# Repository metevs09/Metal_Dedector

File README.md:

# Metal Detector Project

This project provides a comprehensive reference for building a pulse induction metal detector. It includes the general system scheme, hardware design files, PCB designs, CAM files for manufacturing, and a USB to UART module for ESP32 integration.

## Overview
The Metal Detector project is designed to help enthusiasts and professionals understand and implement a pulse induction metal detector. The repository contains:

- General Scheme: Detailed system and hardware schematics.
- PCB Design Files: Ready-to-use designs for fabricating the circuit board.
- CAM Files: Files required for computer-aided manufacturing.
- ESP32 Integration: A USB to UART module for connecting the detector to an ESP32 microcontroller.
## Features
- Pulse Induction Operation: Implements the principles of pulse induction metal detection.
- Detailed Schematics: Complete general and hardware design documents.
- PCB and CAM Files: Design files for PCB manufacturing and assembly.
- ESP32 Interface: Provides a USB to UART bridge for interfacing with ESP32-based systems.
  
## Repository Structure
```
Metal_Dedector/
- ├── CAM file/              # CAM files for PCB manufacturing
- ├── PCB files/             # PCB design files and layouts
- ├── USB to UART for ESP32/  # Interface files for ESP32 integration
- ├── Metal Dedektör.drawio   # Schematic diagram created with draw.io
- ├── README.md              # This README file
- └── SECURITY.md            # Security policy information
```
## Getting Started

### Prerequisites

#### Electronics Knowledge:
- Basic understanding of electronics and PCB design.
#### Software Tools:
- Draw.io for viewing and editing schematics.
- PCB design software (such as Eagle or KiCad) for viewing the PCB files.
- A computer with a USB interface for using the ESP32 integration module.
### Installation
#### Clone the Repository:
```git clone https://github.com/metevs09/Metal_Dedector.git```

#### Review the Design Files:
- Open Metal Dedektör.drawio with Draw.io to view the schematic.
- Check the PCB files in the PCB files/ directory.
- Refer to the files in USB to UART for ESP32/ for ESP32 interfacing details.
#### Manufacture and Assemble:
- Use the CAM files to prepare your PCB for manufacturing.
- Assemble the components following standard electronic assembly practices.
### Usage
Once the hardware is assembled:

1. Connect the ESP32 via the USB to UART interface.
2. Use your preferred development environment to load and run firmware.
3. Test the metal detector according to the provided schematic and design guidelines.
> Note: Always follow proper safety procedures when working with electronic circuits and during the assembly process.

License
This project is licensed under the MIT License. See the LICENSE file for more details.

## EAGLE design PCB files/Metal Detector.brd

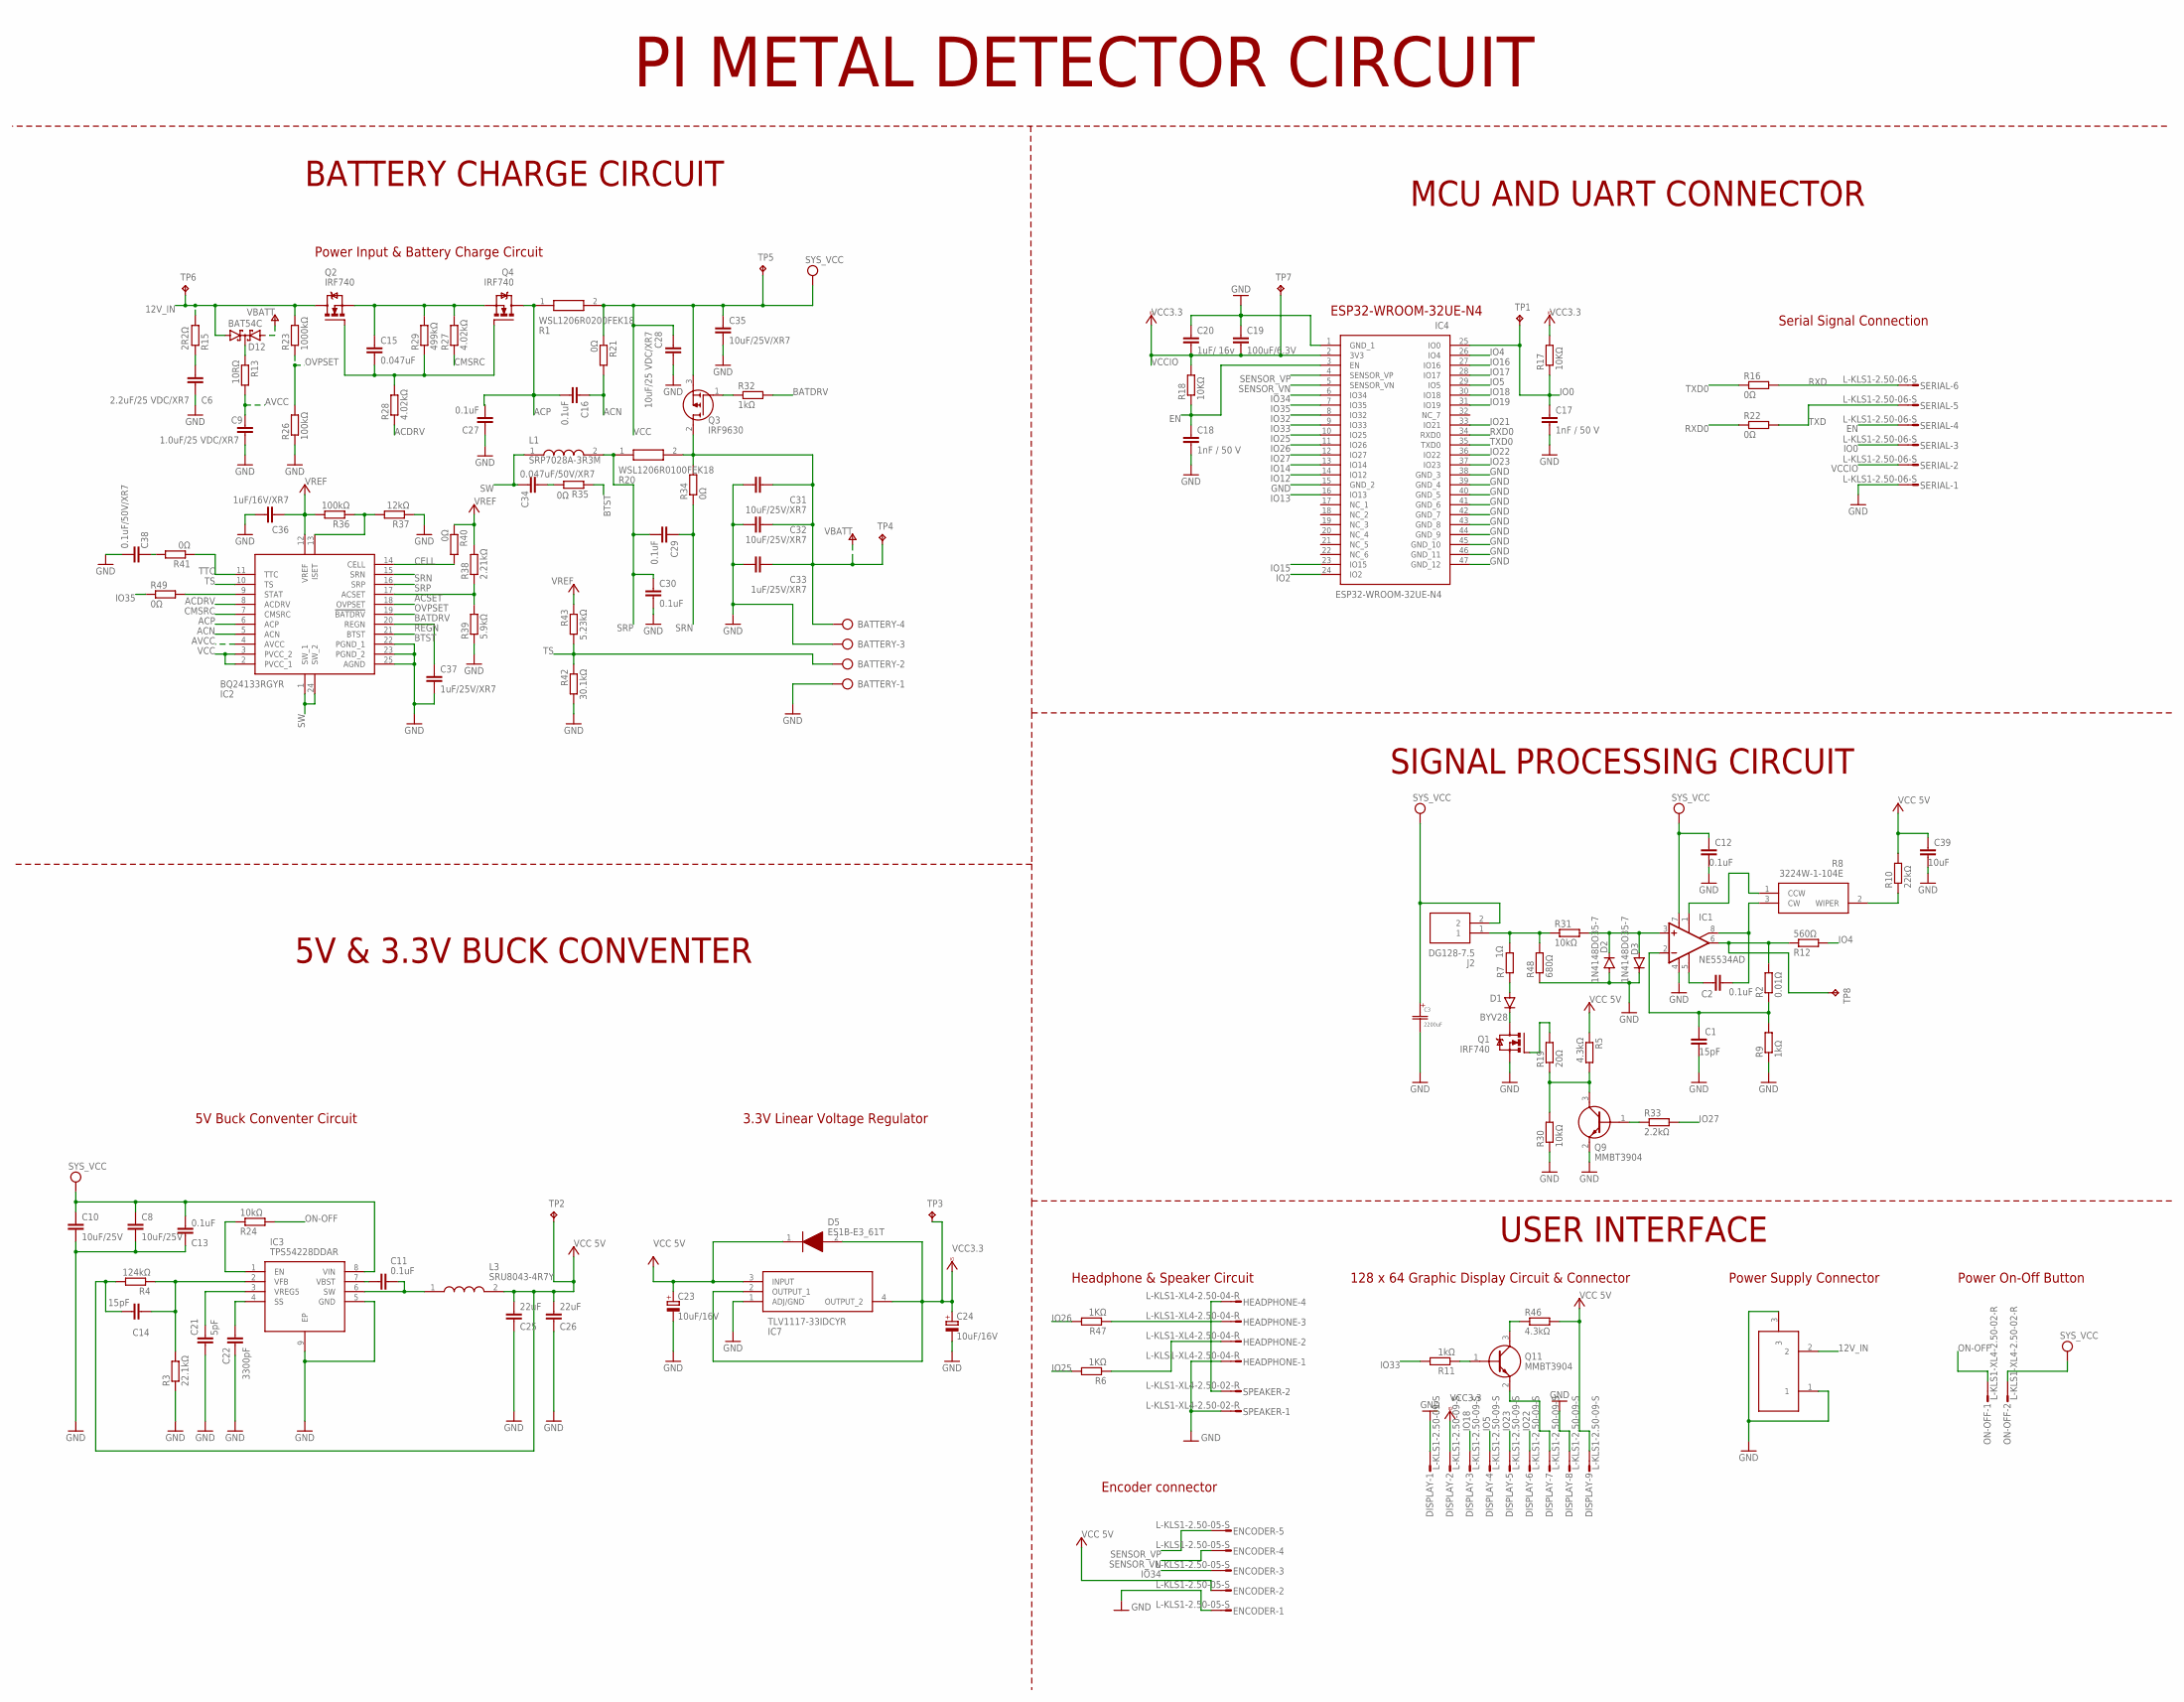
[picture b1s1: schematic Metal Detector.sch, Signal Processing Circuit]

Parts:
12VIN: DC21MMX; DC-21MM
BATTERY: AK500/4
C1, C14: 15pF; C0603
C2, C11, C12, C13, C16, C27, C29, C30: 0.1uF; C0603
C3: 2200uF; CAP_12.5_X_20_PAN
C6: 2.2uF/25 VDC/XR7; 1206
C8, C10: 10uF/25V; C1210
C9: 1.0uF/25 VDC/XR7; 1206
C15: 0.047uF; C0603
C17, C18: 1nF / 50 V; C0603
C19: 100uF/6.3V; C1206
C20: 1uF/ 16v; C0603
C21: 5pF; C0603
C22: 3300pF; C0603
C23, C24: 10uF/16V; PANASONIC_B
C25, C26: 22uF; 1206
C28: 10uF/25 VDC/XR7; 1206
C31, C32, C35: 10uF/25V/XR7; 1206
C33, C37: 1uF/25V/XR7; C0805
C34: 0.047uF/50V/XR7; C0603
C36: 1uF/16V/XR7; C0805
C38: 0.1uF/50V/XR7; C0603
C39: 10uF; C0603
D1: BYV28; SOD64-10
D2, D3: 1N4148DO35-7; DO35-7
D5: ES1B-E3_61T; DIOM5127X229N
D12: BAT54C; SOT23
DISPLAY: L-KLS1-2.50-09-S; S09P
ENCODER: L-KLS1-2.50-05-S; S05P
HEADPHONE: L-KLS1-XL4-2.50-04-R; S04P
IC1: NE5534AD; SO08
IC2: BQ24133RGYR
IC3: TPS54228DDAR; SOIC127P600X170-9N
IC4: ESP32-WROOM-32UE-N4; ESP32WROOM32UEN4
IC7: TLV1117-33IDCYR; SOT230P700X180-4N
J2: DG128-7.5; DG1287502P1400AH
L1: SRP7028A-3R3M; SRP7028A3R3M
L3: SRU8043-4R7Y; SRU8043330Y
ON-OFF: L-KLS1-XL4-2.50-02-R; S02P
Q1, Q2, Q4: IRF740; TO220BV
Q3: IRF9630; TO254P465X1024X2050-3P
Q9, Q11: MMBT3904; SOT95P240X120-3N
R1: WSL1206R0200FEK18; RESC3216X89N
R2: 0.01Ω; R1206
R3: 22.1kΩ; R0603
R4: 124kΩ; R0603
R5, R46: 4.3kΩ; R1206
R6, R47: 1KΩ; R0603
R7: 1Ω; 0207/10
R8: 3224W-1-104E; 3224W-1-105E
R9: 1kΩ; R1206
R10: 22kΩ; R1206
R11, R32: 1kΩ; R0603
R12: 560Ω; R0603
R13: 10RΩ; R1206
R15: 2R2Ω; R2010
R16, R21, R22, R34, R35, R40, R41, R49: 0Ω; R0603
R17, R18: 10KΩ; R0603
R19: 20Ω; R1206
R20: WSL1206R0100FEK18; RESC3216X89N
R23: 1000kΩ; R0603
R24: 10kΩ; R0603
R26, R36: 100kΩ; R0603
R27, R28: 4.02kΩ; R0603
R29: 499kΩ; R0603
R30, R31: 10kΩ; R1206
R33: 2.2kΩ; R1206
R37: 12kΩ; R0603
R38: 2.21kΩ; R0603
R39: 5.9kΩ; R0603
R42: 30.1kΩ; R0603
R43: 5.23kΩ; R0603
R48: 680Ω; R1206
SERIAL: L-KLS1-2.50-06-S; S06P
SPEAKER: L-KLS1-XL4-2.50-02-R; S02P
TP1, TP2, TP3, TP4, TP5, TP6, TP7, TP8: TPTP10R; TP10R

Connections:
12V_IN: 12VIN.2, D12.1 (A1), Q2.D, R15.2, R23.2, TP6.TP
ACDRV: IC2.8 (ACDRV), R28.1
ACN: C16.1, IC2.5 (ACN), R21.2
ACP: C16.2, C27.2, IC2.6 (ACP), Q4.D, R1.1
ACSET: IC2.17 (ACSET), R38.1, R39.2
AVCC: C9.1, IC2.4 (AVCC), R13.2
BATDRV: IC2.19 (!BATDRV), R32.2
BTST: IC2.21 (BTST), R35.1
CELL: IC2.14 (CELL), R40.2
CMSRC: IC2.7 (CMSRC), R27.1
EN: C18.1, IC4.3 (EN), R18.1, SERIAL.4
GND: 12VIN.1, 12VIN.3, BATTERY.1, BATTERY.3, C1.2, C3.2, C6.2, C8.2, C9.2, C10.2, C12.2, C13.2, C17.2, C18.2, C19.1, C20.1, C21.2, C22.2, C23.-, C24.-, C25.2, C26.2, C27.1, C28.2, C30.2, C31.2, C32.2, C33.2, C35.2, C36.1, C37.2, C38.2, C39.2, D2.A, D3.C, DISPLAY.1, DISPLAY.8, ENCODER.1, HEADPHONE.1, IC1.4 (V-), IC2.22 (PGND_1), IC2.23 (PGND_2), IC2.25 (AGND), IC3.5 (GND), IC3.9 (EP), IC4.1 (GND_1), IC4.15 (GND_2), IC4.38 (GND_3), IC4.39 (GND_4), IC4.40 (GND_5), IC4.41 (GND_6), IC4.42 (GND_7), IC4.43 (GND_8), IC4.44 (GND_9), IC4.45 (GND_10), IC4.46 (GND_11), IC4.47 (GND_12), IC7.1 (ADJ/GND), Q1.S, Q9.2 (E), R3.1, R9.1, R26.1, R30.1, R37.1, R39.1, R42.2, R48.1, SERIAL.1, SPEAKER.1
IO0: C17.1, IC4.25 (IO0), R17.1, SERIAL.3, TP1.TP
IO2: IC4.24 (IO2)
IO4: IC1.6 (OUT), IC4.26 (IO4), R2.2, R12.1, R12.2, TP8.TP
IO5: DISPLAY.4, IC4.29 (IO5)
IO12: IC4.14 (IO12)
IO13: IC4.16 (IO13)
IO14: IC4.13 (IO14)
IO15: IC4.23 (IO15)
IO16: IC4.27 (IO16)
IO17: IC4.28 (IO17)
IO18: DISPLAY.3, IC4.30 (IO18)
IO19: IC4.31 (IO19)
IO21: IC4.33 (IO21)
IO22: DISPLAY.6, IC4.36 (IO22)
IO23: DISPLAY.5, IC4.37 (IO23)
IO25: IC4.10 (IO25), R6.2
IO26: IC4.11 (IO26), R47.2
IO27: IC4.12 (IO27), R33.2
IO32: IC4.8 (IO32)
IO33: IC4.9 (IO33), R11.2
IO34: ENCODER.3, IC4.6 (IO34)
IO35: IC2.9 (STAT), IC4.7 (IO35), R49.1, R49.2
ISET: IC2.13 (ISET), R36.1, R37.2
unnamed: D2.C, D3.A, IC1.3 (+IN), R31.2
unnamed: Q1.G, R19.2
unnamed: Q9.3 (C), R5.2, R19.1, R30.2
unnamed: D1.A, R7.1
unnamed: Q9.1 (B), R33.1
unnamed: D1.C, Q1.D
unnamed: J2.1, R7.2, R31.1, R48.2
unnamed: HEADPHONE.2, R6.1
unnamed: IC1.1 (ON), R8.1 (CCW)
unnamed: R8.2 (WIPER), R10.1
unnamed: C2.2, IC1.8 (ON/CMP), R8.3 (CW)
unnamed: C1.1, IC1.2 (-IN), R2.1, R9.2
unnamed: C2.1, IC1.5 (CMP)
unnamed: D12.3 (CC), R13.1
unnamed: DISPLAY.7, Q11.2 (E)
unnamed: C6.1, R15.1
unnamed: IC3.1 (EN), R24.1
unnamed: C11.1, IC3.7 (VBST)
unnamed: C11.2, IC3.6 (SW), L3.1
unnamed: C15.1, Q2.S, Q4.S, R27.2, R29.2
unnamed: C15.2, Q2.G, Q4.G, R28.2, R29.1
unnamed: Q3.1 (G), R32.1
unnamed: C14.1, IC3.2 (VFB), R3.2, R4.1
unnamed: C34.2, R35.2
unnamed: C38.1, R41.2
unnamed: HEADPHONE.4, SPEAKER.2
unnamed: C21.1, IC3.3 (VREG5)
unnamed: Q11.1 (B), R11.1
unnamed: HEADPHONE.3, R47.1
unnamed: C22.1, IC3.4 (SS)
unnamed: Q11.3 (C), R46.1
ON-OFF: ON-OFF.1, R24.2
OVPSET: IC2.18 (OVPSET), R23.1, R26.2
REGN: C37.1, IC2.20 (REGN)
RXD: R16.2, SERIAL.6
RXD0: IC4.34 (RXD0), R22.1
SENSOR_VN: ENCODER.4, IC4.5 (SENSOR_VN)
SENSOR_VP: ENCODER.5, IC4.4 (SENSOR_VP)
SRN: C29.1, IC2.15 (SRN), R34.1
SRP: C29.2, C30.1, IC2.16 (SRP), L1.2, R20.1
SW: C34.1, IC2.1 (SW_1), IC2.24 (SW_2), L1.1
TS: BATTERY.2, IC2.10 (TS), R42.1, R43.2
TTC: IC2.11 (TTC), R41.1
TXD: R22.2, SERIAL.5
TXD0: IC4.35 (TXD0), R16.1
VBATT: BATTERY.4, C31.1, C32.1, C33.1, D12.2 (A2), Q3.2 (D), R20.2, R34.2, TP4.TP
VCC: C3.1, C8.1, C10.1, C12.1, C13.1, C14.2, C23.+, C25.1, C26.1, C28.1, C35.1, C36.2, C39.1, D5.1 (K), DISPLAY.9, ENCODER.2, IC1.7 (V+), IC2.2 (PVCC_1), IC2.3 (PVCC_2), IC2.12 (VREF), IC3.8 (VIN), IC7.3 (INPUT), J2.2, L3.2, ON-OFF.2, Q3.3 (S), R1.2, R4.2, R5.1, R10.2, R21.1, R36.2, R38.2, R40.1, R43.1, R46.2, TP2.TP, TP5.TP
VCCIO: C19.2, C20.2, C24.+, D5.2 (A), DISPLAY.2, IC4.2 (3V3), IC7.2 (OUTPUT_1), IC7.4 (OUTPUT_2), R17.2, R18.2, SERIAL.2, TP3.TP, TP7.TP

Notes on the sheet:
MCU AND UART CONNECTOR
ESP32-WROOM-32UE-N4
BATTERY CHARGE CIRCUIT
SIGNAL PROCESSING CIRCUIT
USER INTERFACE
Power Input & Battery Charge Circuit
Power On-Off Button
128 x 64 Graphic Display Circuit & Connector
Headphone & Speaker Circuit
5V Buck Conventer Circuit
5V & 3.3V BUCK CONVENTER
PI METAL DETECTOR CIRCUIT
Encoder connector
Serial Signal Connection
3.3V Linear Voltage Regulator
Power Supply Connector

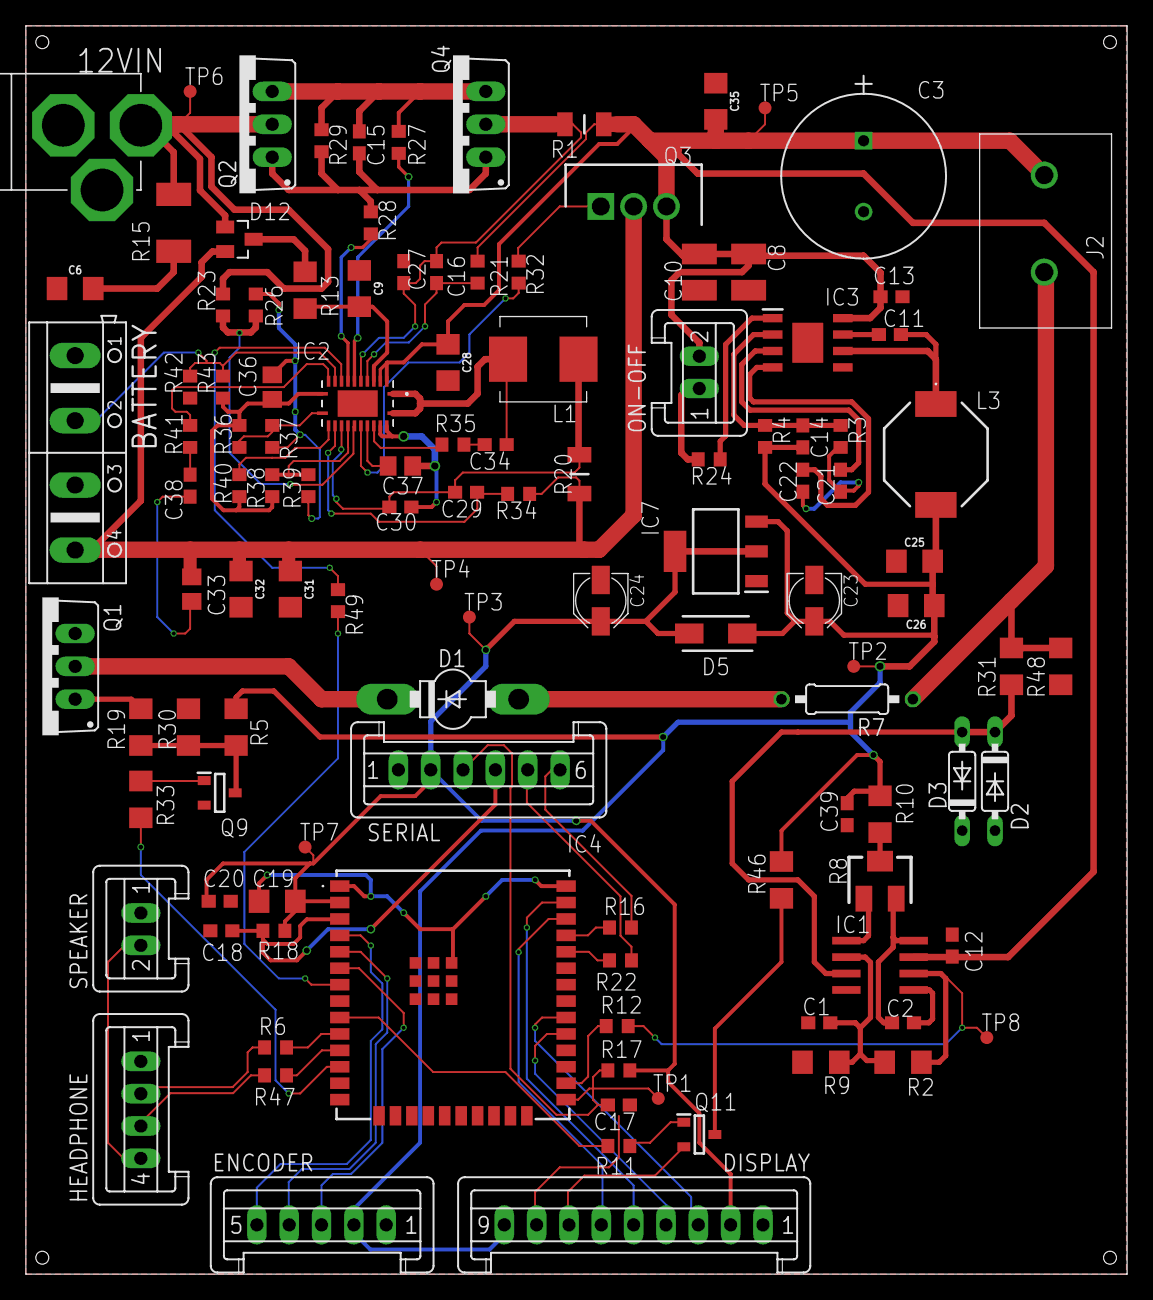
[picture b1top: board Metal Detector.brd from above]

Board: 2 copper layers, 85.1 x 96.5 mm, 116 parts (0 on the bottom side), 73 nets.

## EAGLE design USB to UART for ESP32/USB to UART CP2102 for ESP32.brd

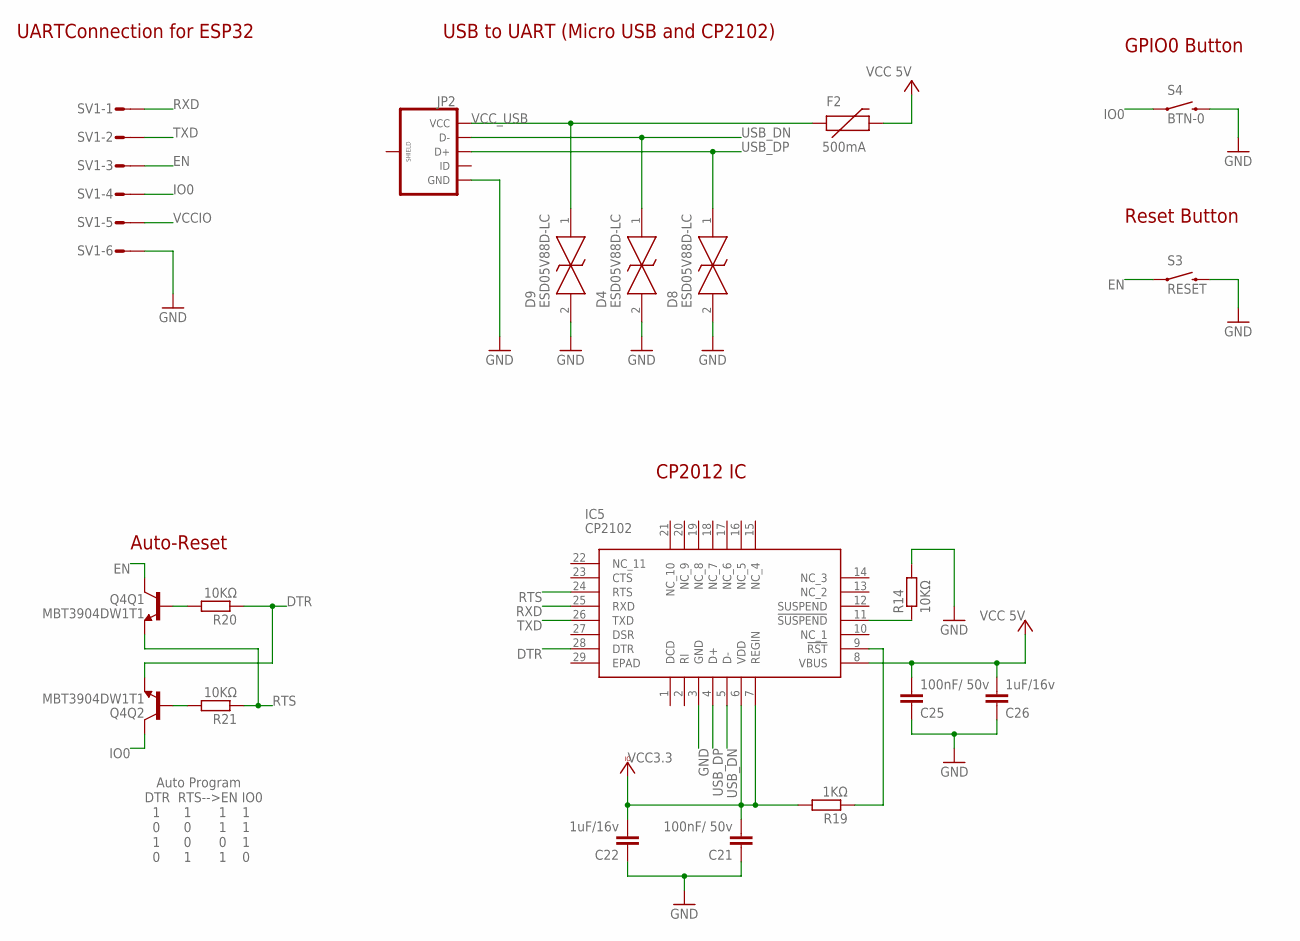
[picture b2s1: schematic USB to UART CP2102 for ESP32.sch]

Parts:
C21, C25: 100nF/ 50v; C0603
C22, C26: 1uF/16v; C0603
D4, D8, D9: ESD05V88D-LC; ESD05V88DLC
F2: 500mA; PTC-1206
IC5: CP2102; QFN50P500X500X100-29N
JP2: USB_MICROB_PLUGCONN-11752; USB-B-MICRO-SMD_V03
Q4: MBT3904DW1T1; SC70-6
R14, R20, R21: 10KΩ; R0603
R19: 1KΩ; R0603
S3: RESET; TACTILE_SWITCH_SMD_4.6X2.8MM
S4: BTN-0; TACTILE_SWITCH_SMD_4.6X2.8MM
SV1: L06P

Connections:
ACTıVE: IC5.11 (!SUSPEND), R14.1
DTR: IC5.28 (DTR), Q4.1 (E), R20.1
EN: Q4.3 (C), S3.1, S3.2 (1), SV1.3
GND: C21.1, C22.1, C25.1, C26.1, D4.2, D8.2, D9.2, IC5.3 (GND), JP2.GND, R14.2, S3.3 (2), S3.4 (2), S4.3 (2), S4.4 (2), SV1.6
IO0: Q4.6 (C), S4.1, S4.2 (1), SV1.4
unnamed: Q4.5 (B), R20.2
unnamed: Q4.2 (B), R21.2
unnamed: IC5.9 (!RST), R19.1
RTS: IC5.24 (RTS), Q4.4 (E), R21.1
RXD: IC5.25 (RXD), SV1.1
TXD: IC5.26 (TXD), SV1.2
USB_DN: D4.1, IC5.5 (D-), JP2.D-
USB_DP: D8.1, IC5.4 (D+), JP2.D+
VCC: C25.2, C26.2, F2.2, IC5.8 (VBUS)
VCCIO: C21.2, C22.2, IC5.6 (VDD), IC5.7 (REGIN), R19.2, SV1.5
VCC_USB: D9.1, F2.1, JP2.VBUS (VCC)

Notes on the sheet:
GPIO0 Button
Reset Button
Auto-Reset
Auto Program DTR RTS-->EN IO0 1 1 1 1 0 0 1 1 1 0 0 1 0 1 1 0
USB to UART (Micro USB and CP2102)
UARTConnection for ESP32
CP2012 IC

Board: 2 copper layers, 18 parts (0 on the bottom side), 16 nets, no tracks yet.

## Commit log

2023-12-19 Metal Detector Main Scheme
2023-12-19 Güncelleme Metal Dedektör.drawio
2023-12-23 Metal Detector PCB
    Still designing Signal Processing Circuit
2023-12-23 Add files via upload
    Still designing signal processing circuit
2023-12-25 Add files via upload
    Adding MCU sheet
2023-12-27 Add files via upload
    Adding MCU peripherals, still designin MCU parts
2023-12-27 Add files via upload
    Completed designing MCU and Peripheral sheet
2023-12-27 Add files via upload
    Adding Subtitle to sheet
2023-12-28 Add files via upload
    Deleted sheet 2 and include content to sheet 1 for software limitations after that edited sheet 1
2023-12-28 Add files via upload
    Added Battery charging & power regulator and User Interface components, created board file.
    Design process still on progress.
2023-12-29 Add files via upload
    Design process still on progress
2023-12-31 Add files via upload
    Still designin power circuit but should be change battery charge IC for tehnical limitation
2024-01-01 Add files via upload
    Adding Voltage Regulator Circuits
2024-01-01 Add files via upload
    Still designing battery charger and power line managment circuit
2024-01-02 Add files via upload
    Still designing battery charge circuit, it is almost over.
2024-01-03 Add files via upload
    Battery Charge Circuit design process is finished but This design is unexpectedly expencive due to peripheral components.
    Founded new IC and will change design for new IC. ( I'm so sorry for that : /) will be more cost effective.
2024-01-04 Add files via upload
    Assigned ISET adn ACSET value for selected battery
2024-01-05 Add files via upload
    Added LCD connections
2024-01-05 Add files via upload
    adding speaker's control circuit (Design process still in progress)
2024-01-06 Add files via upload
    Connected and added Spekers, volume and sensitivty connections with MCU
2024-01-09 Add files via upload
    Redesigned signal processing circuit due to ground layer
2024-01-10 Add files via upload
    Fixed sum bug
2024-01-13 Add files via upload
    Redesigned Regulators Circuit and editing sheet
2024-01-15 Add files via upload
    Redesigned Uaer Interface Block for Encoder (Encoder will include other design step)
2024-01-16 Add files via upload
    Add connector to User Interface
2024-01-19 Add files via upload
    Separated USB to UART part edited User interface and Redesign Buck conventer Circuit for Implementation problem : /
2024-01-19 Add files via upload
    Designed buck conventer and linear voltage regulator circuit and simulated circuit on TI platform next progress change opamp for offset voltage implementation issue and redesign headphone connection 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
2024-01-23 Add files via upload
    Desing process is done, USB to UART brigdge is separated from board, after last power and battery circuit check will get next section
    ,the next section is PCB board design that is the last steps
2024-01-23 Create USB to UART bridge for ESP32
2024-01-23 USB to UART for ESP32
2024-01-23 Create Read
2024-01-23 Add files via upload
    Included USB to UART for ESP32 files
2024-01-23 Add files via upload
    Changed some resistor value for set electrical input parameter on Battery charge IC
2024-01-24 Add files via upload
    Started design PCB layout first start from battery charge circut, still desing process
2024-01-25 Add files via upload
    Battery charge circuit on design progress
2024-01-26 Add files via upload
    Designed Battery charge circut next design power circut and connection two circuit
2024-01-26 Add files via upload
    Removed all component ot board
2024-01-28 Add files via upload
    Optimizated PCB trace and designed 12V to 5V Buck coneventer
2024-01-29 Add files via upload
    Redesign 5V buck conventer circuit for implementation problem
2024-01-29 Add files via upload
    Designed 5V, 3.3V power circuit and signal processing circuit after that repositioned component I will do microprossesor connection and repositioning on next section
2024-01-30 Add files via upload
    All schematic and board design process is done after that upload BOM file, 3rd view docs and manufacturing files
2024-02-01 Gerber Files
2024-02-01 Create drill
2024-02-01 Create assembly
2024-02-01 Create cam
2024-02-05 Add files via upload
    Edited pcb trace nad add test point
2024-02-05 Add files via upload
    Edited pcb layout and removed some via from gnd
2024-02-05 Add files via upload
    Remove some via and edited pcb trace
2025-02-20 Update README.md
    Edited README files
2025-02-20 Update README.md
    Added Picture to README

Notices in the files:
parts and their libraries:
SparkFun-Capacitors: Licensing: Creative Commons ShareAlike 4.0 International - https://creativecommons.org/licenses/by-sa/4.0
COPYRIGHT: Copyright (C) 2024 Ultra Librarian. All rights reserved.
